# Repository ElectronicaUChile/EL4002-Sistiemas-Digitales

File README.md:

# EL4002 Sistiemas Digitales

En el marco de los proyectos finales del curso, en este repositorio se pueden encontrar códigos funcionales para añadir a los proyectos de final del curso, según necesidad. 

### Hardware relacionado

Los proyectos en FPGA son realizados en la tarjeta de desarrollo Spartan 3E, en tanto los de micro-controladores son implementados en PIC18F4550.

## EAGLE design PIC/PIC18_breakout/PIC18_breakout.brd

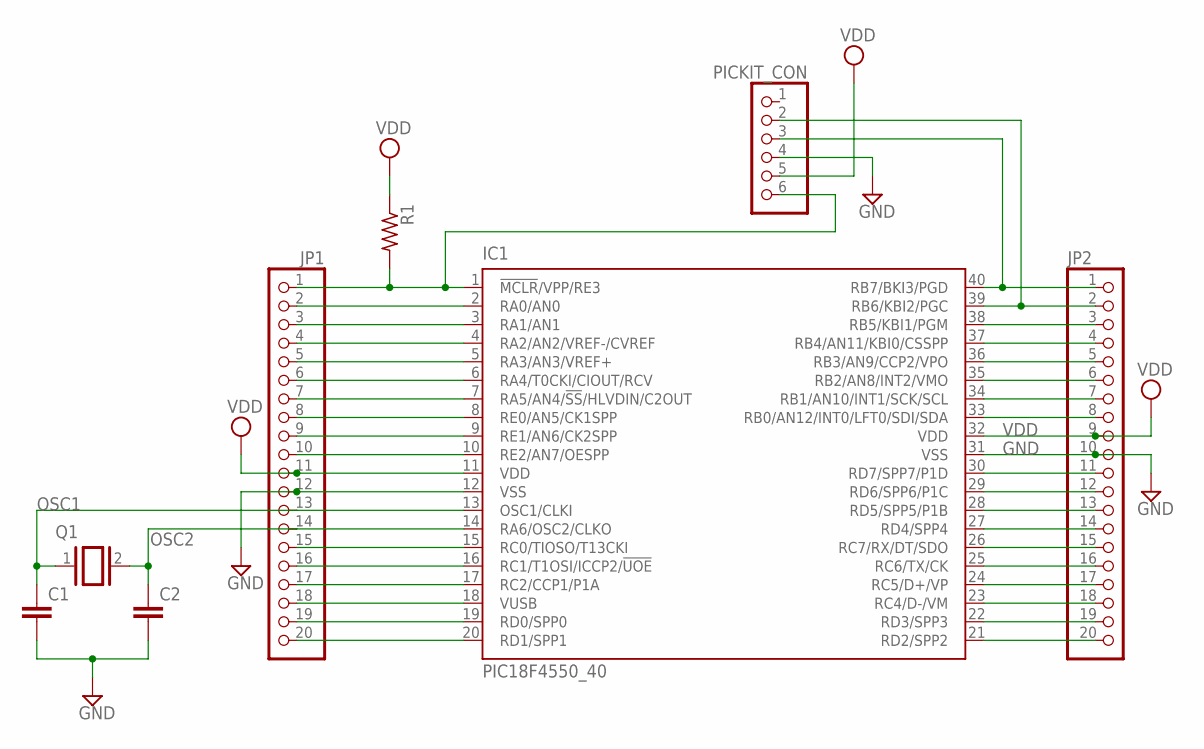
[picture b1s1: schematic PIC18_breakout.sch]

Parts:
C1, C2: C-EU075-032X103; C075-032X103
IC1: PIC18F4550_40; DIL40
JP1, JP2: PINHD-1X20; 1X20
PICKIT_CON: PINHD-1X6/90; 1X06/90
Q1: XTAL/S; QS
R1: R-US_0207/10; 0207/10

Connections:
GND: C1.2, C2.2, IC1.12 (VSS), IC1.31 (VSS), JP1.12, JP2.10, PICKIT_CON.4
unnamed: IC1.2 (RA0/AN0), JP1.2
unnamed: IC1.3 (RA1/AN1), JP1.3
unnamed: IC1.4 (RA2/AN2/VREF-/CVREF), JP1.4
unnamed: IC1.5 (RA3/AN3/VREF+), JP1.5
unnamed: IC1.6 (RA4/T0CKI/CIOUT/RCV), JP1.6
unnamed: IC1.7 (RA5/AN4/!SS!/HLVDIN/C2OUT), JP1.7
unnamed: IC1.8 (RE0/AN5/CK1SPP), JP1.8
unnamed: IC1.9 (RE1/AN6/CK2SPP), JP1.9
unnamed: IC1.10 (RE2/AN7/OESPP), JP1.10
unnamed: IC1.37 (RB4/AN11/KBI0/CSSPP), JP2.4
unnamed: IC1.36 (RB3/AN9/CCP2/VPO), JP2.5
unnamed: IC1.15 (RC0/TIOSO/T13CKI), JP1.15
unnamed: IC1.16 (RC1/T1OSI/ICCP2/!UOE), JP1.16
unnamed: IC1.17 (RC2/CCP1/P1A), JP1.17
unnamed: IC1.18 (VUSB), JP1.18
unnamed: IC1.19 (RD0/SPP0), JP1.19
unnamed: IC1.20 (RD1/SPP1), JP1.20
unnamed: IC1.35 (RB2/AN8/INT2/VMO), JP2.6
unnamed: IC1.34 (RB1/AN10/INT1/SCK/SCL), JP2.7
unnamed: IC1.33 (RB0/AN12/INT0/LFT0/SDI/SDA), JP2.8
unnamed: IC1.30 (RD7/SPP7/P1D), JP2.11
unnamed: IC1.29 (RD6/SPP6/P1C), JP2.12
unnamed: IC1.28 (RD5/SPP5/P1B), JP2.13
unnamed: IC1.27 (RD4/SPP4), JP2.14
unnamed: IC1.26 (RC7/RX/DT/SDO), JP2.15
unnamed: IC1.25 (RC6/TX/CK), JP2.16
unnamed: IC1.24 (RC5/D+/VP), JP2.17
unnamed: IC1.23 (RC4/D-/VM), JP2.18
unnamed: IC1.22 (RD3/SPP3), JP2.19
unnamed: IC1.21 (RD2/SPP2), JP2.20
OSC1: C1.1, IC1.13 (OSC1/CLKI), JP1.13, Q1.1
OSC2: C2.1, IC1.14 (RA6/OSC2/CLKO), JP1.14, Q1.2
PGC: IC1.39 (RB6/KBI2/PGC), JP2.2, PICKIT_CON.2
PGD: IC1.40 (RB7/BKI3/PGD), JP2.1, PICKIT_CON.3
PGM: IC1.38 (RB5/KBI1/PGM), JP2.3
VDD: IC1.11 (VDD), IC1.32 (VDD), JP1.11, JP2.9, PICKIT_CON.5, R1.1
^MCLR/VPP: IC1.1 (!MCLR!/VPP/RE3), JP1.1, PICKIT_CON.6, R1.2

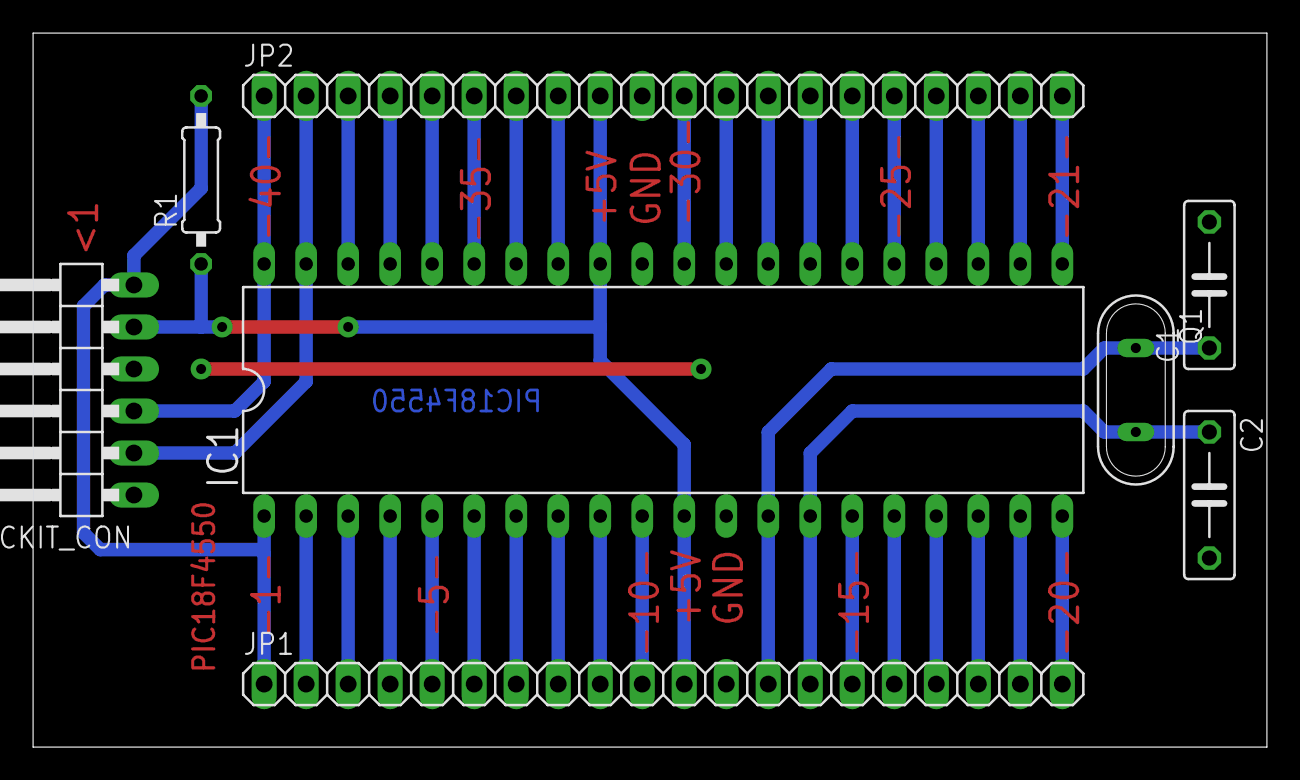
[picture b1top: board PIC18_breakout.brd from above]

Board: 2 copper layers, 74.6 x 43.2 mm, 8 parts (0 on the bottom side), 38 nets.

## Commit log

2016-11-19 Se agregan códigos para implementar ADCs en ambas plataformas
2017-03-11 se agrega diseño de PCB para PIC18
